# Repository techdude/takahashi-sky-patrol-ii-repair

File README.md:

# Takahashi Sky Patrol II Repair and Custom Oscillator
This repository contains some repair and troubleshooting files for the Takahashi Sky Patrol II Power Board and Remote.

It also includes a design for a drop-in replacement MEMS oscillator board in case the crystal oscillator is damaged. This design has been tested and worked on a previous repair, but no warranty is expressed or implied for any of the designs or schematics contained in this repository. Use at your own discretion!

## Repair Resources

Below are several resources that you may find useful when repairing or troubleshooting a Takahashi Sky Patrol 2.

### Remote Board Schematic 
 
You can view the schematic for the Takahashi Sky Patrol II Remote Board here:
 
[📄 Takahashi Sky Patrol 2 Remote Board Schematic (PDF)](schematics/Takahashi%20Sky%20Patrol%202%20Remote%20Board%20Schematic%20Rev%20B.pdf)

### Power Board Schematic

You can view the schematic for the Takahashi Sky Patrol II Power Board here:

[📄 Takahashi Sky Patrol 2 Power Board Schematic (PDF)](schematics/Takahashi%20Sky%20Patrol%202%20Power%20Board%20Schematic%20Rev%20A.pdf)

## Custom Oscillator Board

One component that can go bad on the Takahashi SP2 is the crystal oscillator. Do to the oscillator being a custom frequency, there is no drop-in replacement available. To solve this issue, I designed the following PCB that allows using a factory programmed MEMS oscillator in its place. Once the PCB is assembled, it is a simple drop-in replacement. 

The design contains some power and level translation in addition to the oscillator due to the original chip operating on 5V. For more information on the repair process and decisions, check out the accompanying video of the repair process. 

You can view the schematic for the custom oscillator board here:

[📄 Custom Oscillator Board Schematic (PDF)](schematics/Oscillator%20Board%20Rev%20A.pdf)

The files for the custom board are available [here](oscillator-board).

You can download the Gerber files for the custom oscillator board here:

[📦 Oscillator Board Rev A Gerber Files (ZIP)](oscillator-board/Oscillator%20Board%20Rev%20A%20Gerber.zip)

## Custom Oscillator Board Design and Build Video

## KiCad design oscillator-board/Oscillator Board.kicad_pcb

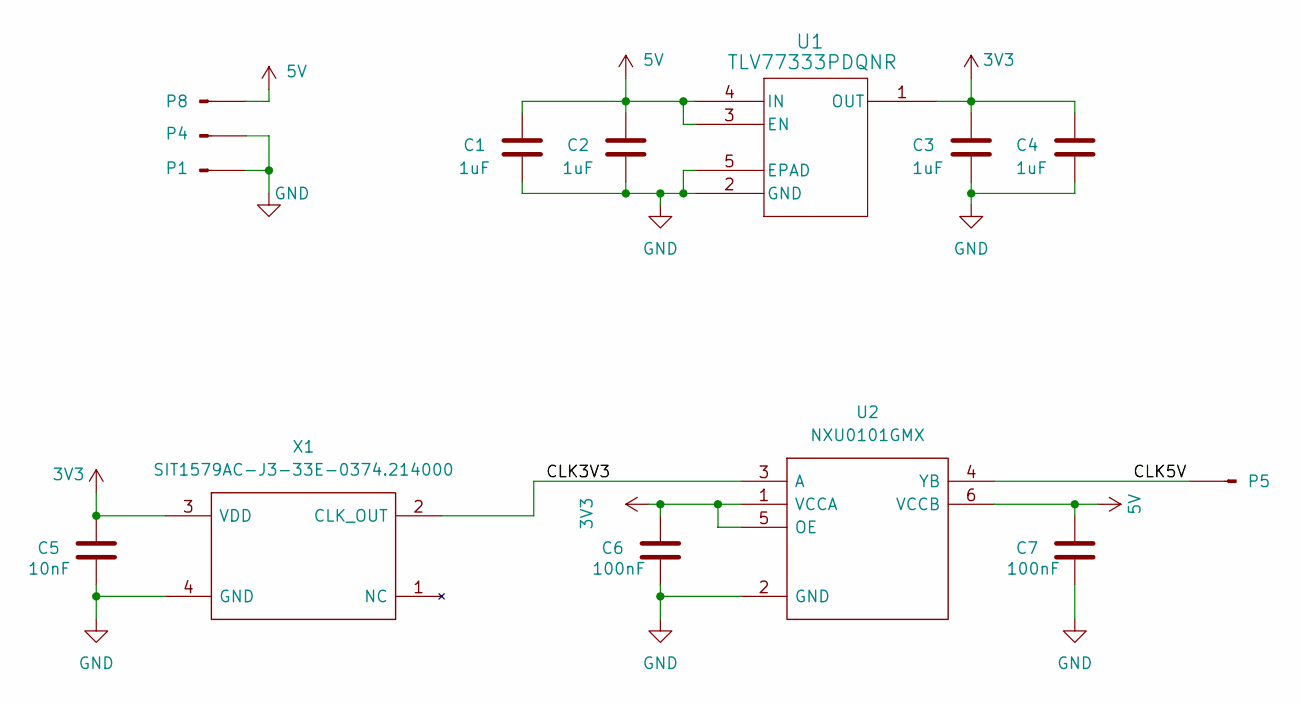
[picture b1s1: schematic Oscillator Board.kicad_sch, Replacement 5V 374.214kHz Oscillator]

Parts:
C1, C2, C3, C4: 1uF; C_0201_0603Metric
C5: 10nF; C_0201_0603Metric
C6, C7: 100nF; C_0201_0603Metric
P1, P4, P5, P8: Conn_01x01_Pin; PinHeader_1x01_P2.54mm_Vertical
U1: TLV77333PDQNR; X2SON_DQN4_TEX
U2: NXU0101GMX; SON50P100X145X50-6N; Manufacturer_Part_Number NXU0101GMX
X1: SIT1579AC-J3-33E-0374.214000; CSP_1508_4pins; Manufacturer_Part_Number SiT1579A-J3-0001

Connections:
3V3: C3.1, C4.1, C5.1, C6.1, U1.1 (OUT), U2.1 (VCCA), U2.5 (OE), X1.3 (VDD)
5V: C1.1, C2.1, C7.1, P8.1, U1.3 (EN), U1.4 (IN), U2.6 (VCCB)
/CLK3V3: U2.3 (A), X1.2 (CLK_OUT)
/CLK5V: P5.1, U2.4 (YB)
GND: C1.2, C2.2, C3.2, C4.2, C5.2, C6.2, C7.2, P1.1, P4.1, U1.2 (GND), U1.5 (EPAD), U2.2 (GND), X1.4 (GND)

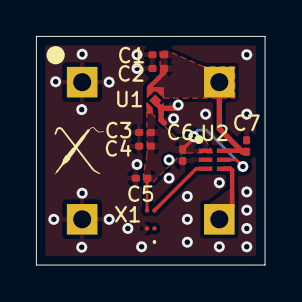
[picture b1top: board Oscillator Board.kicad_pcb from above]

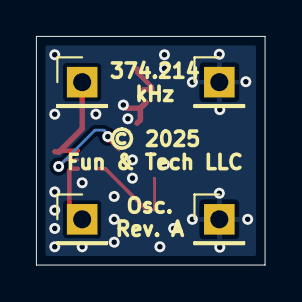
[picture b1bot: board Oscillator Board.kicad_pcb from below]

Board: 2 copper layers, 12.7 x 12.7 mm, 14 parts (4 on the bottom side), 5 nets.

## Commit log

2025-06-21 Add LICENSE
2025-06-21 Initial commit with design files

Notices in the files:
oscillator-board/Oscillator Board.kicad_pcb:
© 2025
